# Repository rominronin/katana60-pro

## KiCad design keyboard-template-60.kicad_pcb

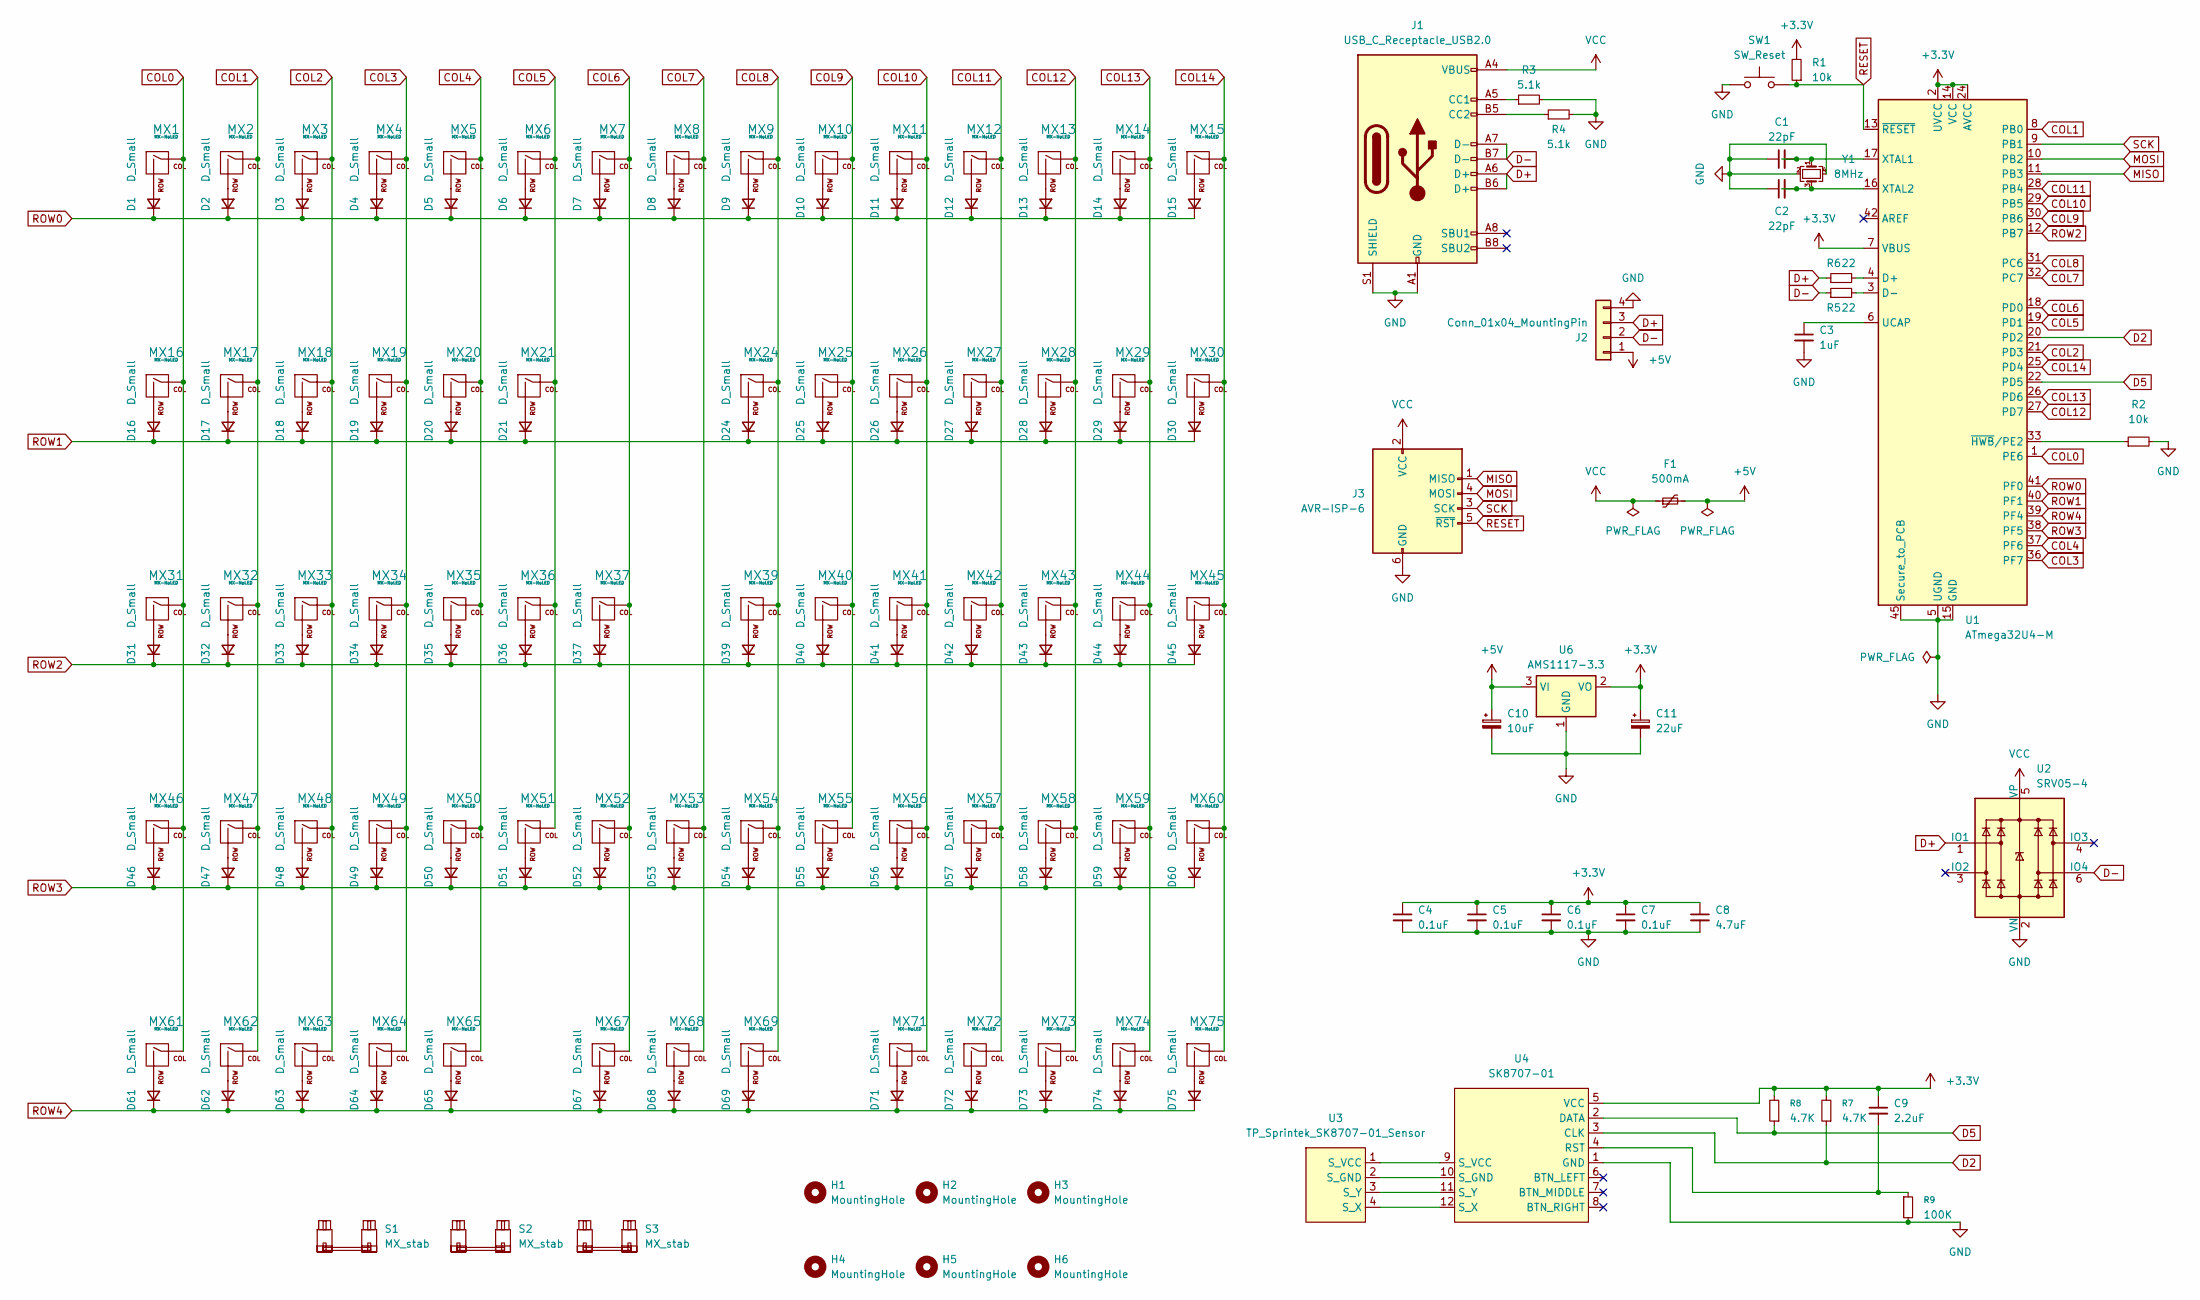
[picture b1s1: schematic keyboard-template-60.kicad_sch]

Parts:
C1, C2: 22pF; C_0603_1608Metric_Pad1.08x0.95mm_HandSolder
C3: 1uF; C_0603_1608Metric_Pad1.08x0.95mm_HandSolder
C4, C5, C6, C7: 0.1uF; C_0603_1608Metric_Pad1.08x0.95mm_HandSolder
C8: 4.7uF; C_0603_1608Metric_Pad1.08x0.95mm_HandSolder
C9: 2.2uF; C_0603_1608Metric_Pad1.08x0.95mm_HandSolder
C10: 10uF; CP_EIA-1608-08_AVX-J
C11: 22uF; CP_EIA-1608-08_AVX-J
D1, D2, D3, D4, D5, D6, D7, D8, D9, D10, D11, D12, D13, D14, D15, D16, D17, D18, D19, D20, D21, D24, D25, D26, D27, D28, D29, D30, D31, D32, D33, D34, D35, D36, D37, D39, D40, D41, D42, D43, D44, D45, D46, D47, D48, D49, D50, D51, D52, D53, D54, D55, D56, D57, D58, D59, D60, D61, D62, D63, D64, D65, D67, D68, D69, D71, D72, D73, D74, D75: D_Small; D_SOD-123
F1: 500mA; Fuse_1206_3216Metric_Pad1.42x1.75mm_HandSolder
H1, H2, H3, H4, H5, H6: MountingHole; MountingHole_2.5mm
J1: USB_C_Receptacle_USB2.0; USB_C_Receptacle_HRO_TYPE-C-31-M-12
J2: Conn_01x04_MountingPin; JST_ACH_BM04B-ACHSS-A-GAN-ETF_1x04-1MP_P1.20mm_Vertical
J3: AVR-ISP-6; PinHeader_2x03_P2.54mm_Horizontal
MX1, MX2, MX3, MX4, MX5, MX6, MX7, MX8, MX9, MX10, MX11, MX12, MX13, MX14, MX15, MX16, MX17, MX18, MX19, MX20, MX21, MX24, MX25, MX26, MX27, MX28, MX29, MX30, MX31, MX32, MX33, MX34, MX35, MX36, MX37, MX39, MX40, MX41, MX42, MX43, MX44, MX45, MX46, MX47, MX48, MX49, MX50, MX51, MX52, MX53, MX54, MX55, MX56, MX57, MX58, MX59, MX60, MX61, MX62, MX63, MX64, MX65, MX67, MX68, MX69, MX71, MX72, MX73, MX74, MX75: MX-NoLED; SW_MX_HS_CPG151101S11_1u
R1, R2: 10k; C_0603_1608Metric_Pad1.08x0.95mm_HandSolder
R3, R4: 5.1k; C_0603_1608Metric_Pad1.08x0.95mm_HandSolder
R5, R6: 22; C_0603_1608Metric_Pad1.08x0.95mm_HandSolder
R7, R8: 4.7K; C_0603_1608Metric_Pad1.08x0.95mm_HandSolder
R9: 100K; C_0603_1608Metric_Pad1.08x0.95mm_HandSolder
S1, S2: MX_stab; STAB_MX_2u
S3: MX_stab; STAB_MX_7u
SW1: SW_Reset; SW_SPST_SKQG_WithStem
U1: ATmega32U4-M; QFN-44-1EP_7x7mm_P0.5mm_EP5.15x5.15mm
U2: SRV05-4; SOT-23-6
U3: TP_Sprintek_SK8707-01_Sensor; TP_Sprintek_SK8707-01-008_Sensor
U4: SK8707-01; TP_Sprintek_SK8707-01
U6: AMS1117-3.3; SOT-223-3_TabPin2
Y1: 8MHz; Crystal_SMD_3225-4Pin_3.2x2.5mm

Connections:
+3.3V: C4.1, C5.1, C6.1, C7.1, C8.1, C9.1, C11.1, R1.2, R7.2, R8.2, U1.2 (UVCC), U1.7 (VBUS), U1.14 (VCC), U1.24 (AVCC), U1.34 (VCC), U1.44 (AVCC), U4.5 (VCC), U6.2 (VO)
+5V: C10.1, F1.2, J2.1, U6.3 (VI)
COL0: MX1.1 (COL), MX16.1 (COL), MX31.1 (COL), MX46.1 (COL), MX61.1 (COL), U1.1 (PE6)
COL1: MX2.1 (COL), MX17.1 (COL), MX32.1 (COL), MX47.1 (COL), MX62.1 (COL), U1.8 (PB0)
COL2: MX3.1 (COL), MX18.1 (COL), MX33.1 (COL), MX48.1 (COL), MX63.1 (COL), U1.21 (PD3)
COL3: MX4.1 (COL), MX19.1 (COL), MX34.1 (COL), MX49.1 (COL), MX64.1 (COL), U1.36 (PF7)
COL4: MX5.1 (COL), MX20.1 (COL), MX35.1 (COL), MX50.1 (COL), MX65.1 (COL), U1.37 (PF6)
COL5: MX6.1 (COL), MX21.1 (COL), MX36.1 (COL), MX51.1 (COL), U1.19 (PD1)
COL6: MX7.1 (COL), MX37.1 (COL), MX52.1 (COL), MX67.1 (COL), U1.18 (PD0)
COL7: MX8.1 (COL), MX53.1 (COL), MX68.1 (COL), U1.32 (PC7)
COL8: MX9.1 (COL), MX24.1 (COL), MX39.1 (COL), MX54.1 (COL), MX69.1 (COL), U1.31 (PC6)
COL9: MX10.1 (COL), MX25.1 (COL), MX40.1 (COL), MX55.1 (COL), U1.30 (PB6)
COL10: MX11.1 (COL), MX26.1 (COL), MX41.1 (COL), MX56.1 (COL), MX71.1 (COL), U1.29 (PB5)
COL11: MX12.1 (COL), MX27.1 (COL), MX42.1 (COL), MX57.1 (COL), MX72.1 (COL), U1.28 (PB4)
COL12: MX13.1 (COL), MX28.1 (COL), MX43.1 (COL), MX58.1 (COL), MX73.1 (COL), U1.27 (PD7)
COL13: MX14.1 (COL), MX29.1 (COL), MX44.1 (COL), MX59.1 (COL), MX74.1 (COL), U1.26 (PD6)
COL14: MX15.1 (COL), MX30.1 (COL), MX45.1 (COL), MX60.1 (COL), MX75.1 (COL), U1.25 (PD4)
D2: R7.1, U1.20 (PD2), U4.3 (CLK)
D5: R8.1, U1.22 (PD5), U4.2 (DATA)
D+: J1.A6 (D+), J1.B6 (D+), J2.3, R6.1, U2.1 (IO1)
D-: J1.A7 (D-), J1.B7 (D-), J2.2, R5.1, U2.6 (IO4)
GND: C1.1, C2.1, C3.2, C4.2, C5.2, C6.2, C7.2, C8.2, C10.2, C11.2, J1.A1 (GND), J1.A12 (GND), J1.B1 (GND), J1.B12 (GND), J1.S1 (SHIELD), J2.4, J3.6 (GND), R2.2, R3.2, R4.2, R9.2, SW1.1, U1.5 (UGND), U1.15 (GND), U1.23 (GND), U1.35 (GND), U1.43 (GND), U1.45 (Secure_to_PCB), U2.2 (VN), U4.1 (GND), U6.1 (GND), Y1.2, Y1.4
MISO: J3.1 (MISO), U1.11 (PB3)
MOSI: J3.4 (MOSI), U1.10 (PB2)
unnamed: D1.2 (A), MX1.2 (ROW)
unnamed: D2.2 (A), MX2.2 (ROW)
unnamed: D3.2 (A), MX3.2 (ROW)
unnamed: D4.2 (A), MX4.2 (ROW)
unnamed: D5.2 (A), MX5.2 (ROW)
unnamed: D6.2 (A), MX6.2 (ROW)
unnamed: D7.2 (A), MX7.2 (ROW)
unnamed: D8.2 (A), MX8.2 (ROW)
unnamed: D9.2 (A), MX9.2 (ROW)
unnamed: D10.2 (A), MX10.2 (ROW)
unnamed: D11.2 (A), MX11.2 (ROW)
unnamed: D12.2 (A), MX12.2 (ROW)
unnamed: D13.2 (A), MX13.2 (ROW)
unnamed: D14.2 (A), MX14.2 (ROW)
unnamed: D15.2 (A), MX15.2 (ROW)
unnamed: D16.2 (A), MX16.2 (ROW)
unnamed: D17.2 (A), MX17.2 (ROW)
unnamed: D18.2 (A), MX18.2 (ROW)
unnamed: D19.2 (A), MX19.2 (ROW)
unnamed: D20.2 (A), MX20.2 (ROW)
unnamed: D21.2 (A), MX21.2 (ROW)
unnamed: D24.2 (A), MX24.2 (ROW)
unnamed: D25.2 (A), MX25.2 (ROW)
unnamed: D26.2 (A), MX26.2 (ROW)
unnamed: D27.2 (A), MX27.2 (ROW)
unnamed: D28.2 (A), MX28.2 (ROW)
unnamed: D29.2 (A), MX29.2 (ROW)
unnamed: D30.2 (A), MX30.2 (ROW)
unnamed: D31.2 (A), MX31.2 (ROW)
unnamed: D32.2 (A), MX32.2 (ROW)
unnamed: D33.2 (A), MX33.2 (ROW)
unnamed: D34.2 (A), MX34.2 (ROW)
unnamed: D35.2 (A), MX35.2 (ROW)
unnamed: D36.2 (A), MX36.2 (ROW)
unnamed: D37.2 (A), MX37.2 (ROW)
unnamed: D39.2 (A), MX39.2 (ROW)
unnamed: D40.2 (A), MX40.2 (ROW)
unnamed: D41.2 (A), MX41.2 (ROW)
unnamed: D42.2 (A), MX42.2 (ROW)
unnamed: D43.2 (A), MX43.2 (ROW)
unnamed: D44.2 (A), MX44.2 (ROW)
unnamed: D45.2 (A), MX45.2 (ROW)
unnamed: D46.2 (A), MX46.2 (ROW)
unnamed: D47.2 (A), MX47.2 (ROW)
unnamed: D48.2 (A), MX48.2 (ROW)
unnamed: D49.2 (A), MX49.2 (ROW)
unnamed: D50.2 (A), MX50.2 (ROW)
unnamed: D51.2 (A), MX51.2 (ROW)
unnamed: D52.2 (A), MX52.2 (ROW)
unnamed: D53.2 (A), MX53.2 (ROW)
unnamed: D54.2 (A), MX54.2 (ROW)
unnamed: D55.2 (A), MX55.2 (ROW)
unnamed: D56.2 (A), MX56.2 (ROW)
unnamed: D57.2 (A), MX57.2 (ROW)
unnamed: D58.2 (A), MX58.2 (ROW)
unnamed: D59.2 (A), MX59.2 (ROW)
unnamed: D60.2 (A), MX60.2 (ROW)
unnamed: D61.2 (A), MX61.2 (ROW)
unnamed: D62.2 (A), MX62.2 (ROW)
unnamed: D63.2 (A), MX63.2 (ROW)
unnamed: D64.2 (A), MX64.2 (ROW)
unnamed: D65.2 (A), MX65.2 (ROW)
unnamed: D67.2 (A), MX67.2 (ROW)
unnamed: D68.2 (A), MX68.2 (ROW)
unnamed: D69.2 (A), MX69.2 (ROW)
unnamed: D71.2 (A), MX71.2 (ROW)
unnamed: D72.2 (A), MX72.2 (ROW)
unnamed: D73.2 (A), MX73.2 (ROW)
unnamed: D74.2 (A), MX74.2 (ROW)
unnamed: D75.2 (A), MX75.2 (ROW)
unnamed: J1.A5 (CC1), R3.1
unnamed: J1.B5 (CC2), R4.1
unnamed: R6.2, U1.4 (D+)
unnamed: R5.2, U1.3 (D-)
unnamed: C3.1, U1.6 (UCAP)
unnamed: C1.2, U1.17 (XTAL1), Y1.1
unnamed: C2.2, U1.16 (XTAL2), Y1.3
unnamed: R2.1, U1.33 (~HWB/PE2)
unnamed: U3.2 (S_GND), U4.10 (S_GND)
unnamed: U3.1 (S_VCC), U4.9 (S_VCC)
unnamed: U3.4 (S_X), U4.12 (S_X)
unnamed: U3.3 (S_Y), U4.11 (S_Y)
unnamed: C9.2, R9.1, U4.4 (RST)
RESET: J3.5 (~RST), R1.1, SW1.2, U1.13 (~RESET)
ROW0: D1.1 (K), D2.1 (K), D3.1 (K), D4.1 (K), D5.1 (K), D6.1 (K), D7.1 (K), D8.1 (K), D9.1 (K), D10.1 (K), D11.1 (K), D12.1 (K), D13.1 (K), D14.1 (K), D15.1 (K), U1.41 (PF0)
ROW1: D16.1 (K), D17.1 (K), D18.1 (K), D19.1 (K), D20.1 (K), D21.1 (K), D24.1 (K), D25.1 (K), D26.1 (K), D27.1 (K), D28.1 (K), D29.1 (K), D30.1 (K), U1.40 (PF1)
ROW2: D31.1 (K), D32.1 (K), D33.1 (K), D34.1 (K), D35.1 (K), D36.1 (K), D37.1 (K), D39.1 (K), D40.1 (K), D41.1 (K), D42.1 (K), D43.1 (K), D44.1 (K), D45.1 (K), U1.12 (PB7)
ROW3: D46.1 (K), D47.1 (K), D48.1 (K), D49.1 (K), D50.1 (K), D51.1 (K), D52.1 (K), D53.1 (K), D54.1 (K), D55.1 (K), D56.1 (K), D57.1 (K), D58.1 (K), D59.1 (K), D60.1 (K), U1.38 (PF5)
ROW4: D61.1 (K), D62.1 (K), D63.1 (K), D64.1 (K), D65.1 (K), D67.1 (K), D68.1 (K), D69.1 (K), D71.1 (K), D72.1 (K), D73.1 (K), D74.1 (K), D75.1 (K), U1.39 (PF4)
SCK: J3.3 (SCK), U1.9 (PB1)
VCC: F1.1, J1.A4 (VBUS), J1.A9 (VBUS), J1.B4 (VBUS), J1.B9 (VBUS), J3.2 (VCC), U2.5 (VP)

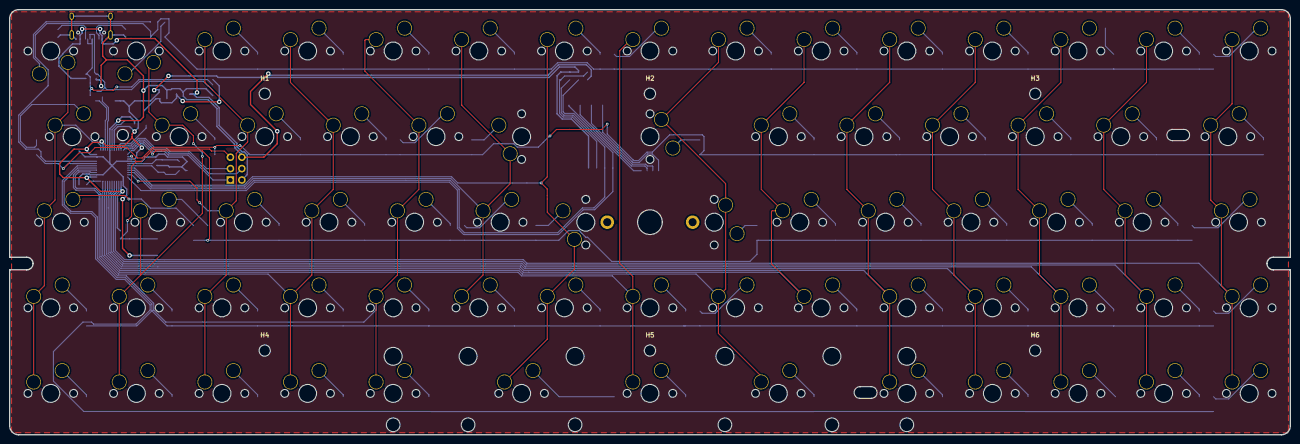
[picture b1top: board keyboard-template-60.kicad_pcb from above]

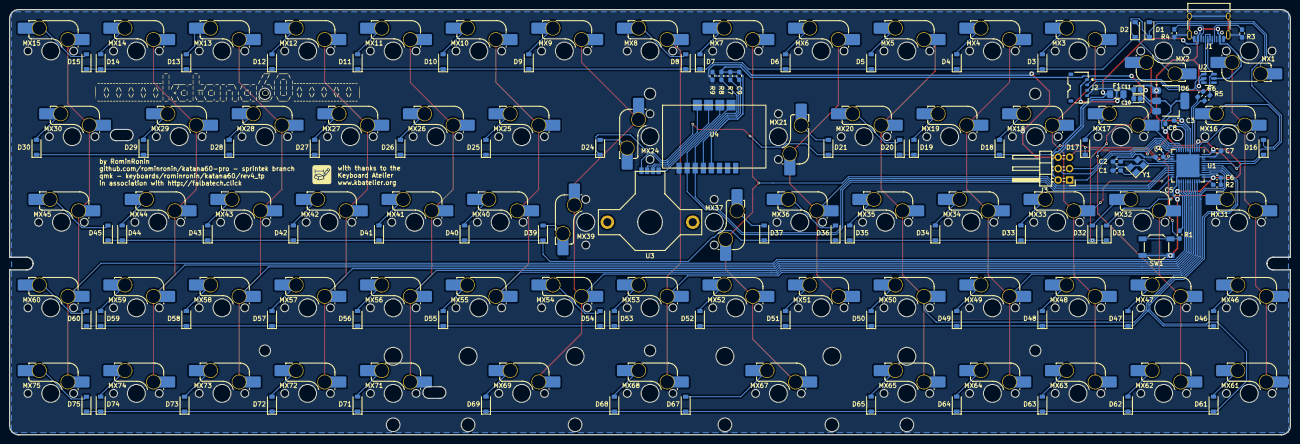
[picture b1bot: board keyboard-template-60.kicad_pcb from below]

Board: 2 copper layers, 285.0 x 94.6 mm, 180 parts (171 on the bottom side), 115 nets.

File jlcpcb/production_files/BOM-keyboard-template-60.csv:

Comment,Designator,Footprint,LCSC,Quantity
0.1uF,"C4,C5,C6,C7",C_0603_1608Metric_Pad1.08x0.95mm_HandSolder,C14663,4
100K,R9,C_0603_1608Metric_Pad1.08x0.95mm_HandSolder,C25803,1
10k,"R1,R2",C_0603_1608Metric_Pad1.08x0.95mm_HandSolder,C25804,2
10uF,C10,CP_EIA-1608-08_AVX-J,C2158420,1
1uF,C3,C_0603_1608Metric_Pad1.08x0.95mm_HandSolder,C15849,1
2.2uF,C9,C_0603_1608Metric_Pad1.08x0.95mm_HandSolder,C23630,1
22,"R5,R6",C_0603_1608Metric_Pad1.08x0.95mm_HandSolder,C23345,2
22pF,"C1,C2",C_0603_1608Metric_Pad1.08x0.95mm_HandSolder,C1653,2
22uF,C11,CP_EIA-1608-08_AVX-J,C2158410,1
4.7K,"R7,R8",C_0603_1608Metric_Pad1.08x0.95mm_HandSolder,C23162,2
4.7uF,C8,C_0603_1608Metric_Pad1.08x0.95mm_HandSolder,C19666,1
5.1k,"R3,R4",C_0603_1608Metric_Pad1.08x0.95mm_HandSolder,C23186,2
500mA,F1,Fuse_1206_3216Metric_Pad1.42x1.75mm_HandSolder,C69688,1
8MHz,Y1,Crystal_SMD_3225-4Pin_3.2x2.5mm,C2682775,1
AMS1117-3.3,U6,SOT-223-3_TabPin2,C6186,1
ATmega32U4-M,U1,QFN-44-1EP_7x7mm_P0.5mm_EP5.15x5.15mm,C112161,1
Conn_01x04_MountingPin,J2,JST_ACH_BM04B-ACHSS-A-GAN-ETF_1x04-1MP_P1.20mm_Vertical,C528030,1
D_Small,"D1,D10,D11,D12,D13,D14,D15,D16,D17,D18,D19,D2,D20,D21,D24,D25,D26,D27,D28,D29,D3,D30,D31,D32,D33,D34,D35,D36,D37,D39,D4,D40,D41,D42,D43,D44,D45,D46,D47,D48,D49,D5,D50,D51,D52,D53,D54,D55,D56,D57,D58,D59,D6,D60,D61,D62,D63,D64,D65,D67,D68,D69,D7,D71,D72,D73,D74,D75,D8,D9",D_SOD-123,C81598,70
MX-NoLED,"MX1,MX10,MX11,MX12,MX13,MX14,MX15,MX16,MX17,MX18,MX19,MX2,MX20,MX21,MX24,MX25,MX26,MX27,MX28,MX29,MX3,MX30,MX31,MX32,MX33,MX34,MX35,MX36,MX37,MX39,MX4,MX40,MX41,MX42,MX43,MX44,MX45,MX46,MX47,MX48,MX49,MX5,MX50,MX51,MX52,MX53,MX54,MX55,MX56,MX57,MX58,MX59,MX6,MX60,MX61,MX62,MX63,MX64,MX65,MX67,MX68,MX69,MX7,MX71,MX72,MX73,MX74,MX75,MX8,MX9",SW_MX_HS_CPG151101S11_1u,C41430893,70
SRV05-4,U2,SOT-23-6,C85364,1
SW_Reset,SW1,SW_SPST_SKQG_WithStem,C318884,1
USB_C_Receptacle_USB2.0,J1,USB_C_Receptacle_HRO_TYPE-C-31-M-12,C165948,1

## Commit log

2022-10-26 create the KiCad project
2022-10-26 add Type-C and MX_Alps_Hybrid libraries
2022-10-26 Move submodules
2022-10-26 add libraries to schematic and pcb apps
2022-12-11 Add new library
2022-12-11 Add marbastlib to repo
2022-12-11 Update schematic
2022-12-17 commit latest work
2022-12-17 tidy up the schematic
2022-12-17 Create a bare matric template
2022-12-17 Update matrix for Katana60 Pro
2022-12-17 Resize tag label size.
2022-12-17 Part annotations
2022-12-17 Update annotations
2022-12-17 Add power flag
2022-12-18 Refactor the alternative switch positions
2022-12-18 Swapped the JST connector
2022-12-18 Assign components
2022-12-18 Place initial PCB parts
2022-12-18 Place PCB outline and parts
2022-12-18 Continue placing parts
2022-12-23 Update the schematic and fix the order of footprints on the PCB
2023-01-21 Update the gs
2023-01-21 Update outline file
2023-01-21 Continue placing components on PCB
2023-02-12 Updates to PCB
2023-02-12 Reposition the diodes, place the fuse, JST socket and reset switch
2023-02-12 Further placement of components
2023-02-12 All parts placed, submit for checks
2023-02-12 Fixed a bug in the schematic
2023-02-27 Start tracing
2023-03-31 Updated the PCB outline footprint
2023-04-02 Update outline footprint, create new edge cut holes
2023-05-03 Final traces, first draft.
2023-05-03 Update the USB C footprint edge cuts
2023-05-05 Update MCU footprint GND new
2023-05-06 Gerbers
2023-05-07 Update schematics and BOM
2023-05-11 Updates to the PCB layout
2023-05-12 Add images backup
2023-05-12 Latest changes
2023-05-13 Update parts assignment and BOM
2023-05-15 Update BOM, retrace JST, re-trace for consistency
2023-05-15 Update reset switch part
2023-05-16 Retrace crystal, caps and reset switch
2023-05-17 Final layout for prototype
2023-05-18 Update images, models and production files
2023-05-18 Update the JST model path
2023-05-19 Update PCB
2023-05-19 Update production files
2023-05-19 Update BOM and footprint names
2023-05-19 Truncate the BOM
2023-05-20 Updated production files
2024-01-13 Update USB-C footprint and routing
2024-01-21 removed gerber files from repo
2024-01-21 Repaired the BOM
2024-01-21 Add mounting holes and re-export productions files
2024-01-22 Save changes
2024-01-23 Updated BOM and production files
2024-01-25 SIP socket placement
2024-01-26 Relocate mounting holes
2024-02-04 Update libraries, reposition ISP footprint, retrace
2024-02-04 Update BOM
2024-03-05 Final changes before getting a second pair of eyes
2026-02-06 introduce trackpoint files and placement - VERY ROUGH WIP
2026-02-24 Integration of trackpoint, regulator and shifter
2026-03-03 Tracing of the new schematic layout
2026-03-05 More retracing
2026-03-09 updated traces, components
2026-03-10 Reposition the parts, begin retracing
2026-03-10 More changes, new footprint, more tracing
2026-03-12 Updates based on the 008
2026-03-12 New production files
2026-03-12 Created fabrication files (for plate generation)
2026-03-12 Create fabrication files
2026-03-12 Updated traces and gerbers
2026-03-13 Continued retracing of components. Nearly finished
2026-03-15 Last commit before DRC begins
2026-03-15 first round of DRC
2026-03-16 finished first round of DRC and fixes
2026-03-16 export production files
2026-03-16 fixed another DRC rule
2026-03-16 recreate fabrication files
2026-03-16 Both trackpoint parts on the same side
2026-03-16 Add fail-safe connector and re-export fabrication files
2026-03-17 Updated BOM for quotation
2026-03-18 Review polarisation of regulator caps, recreate fabrication files
2026-03-31 Retraced some of the errors, removed redundant parts
2026-03-31 Re-export production files
2026-04-01 tidy up some of the traces, rotate the part labels
2026-04-07 Latest export, with fixes
2026-04-08 Reexport production files, after aligning the logo
2026-04-08 Restore standoff holes
2026-04-08 Export for second prototype
